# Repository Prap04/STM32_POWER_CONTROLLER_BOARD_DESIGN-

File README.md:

# STM32F103 Custom Control Board (PCB Project)

This project is a **custom-made PCB (Printed Circuit Board)** built around the **STM32F103C8T6 microcontroller**.  
The goal of this project was to learn how to design a **real hardware board** instead of only using ready-made development boards.

---

## Project Goal

To design a working STM32 board that includes:

- Stable power supply
- Communication ports (CAN, UART, I2C)
- Debugging support
- A PCB that is ready for manufacturing

---

## Main Components Used

| Part | What it Does |
|------|---------------|
| STM32F103C8T6 | Main microcontroller (the brain of the board) |
| CAN Transceiver | Allows CAN communication (used in robotics & industry) |
| UART Header | Used for serial communication and debugging |
| I2C Pins | Used to connect sensors |
| SWD Pins (SWIO, SWCLK) | Used to upload and debug firmware |
| Capacitors | Reduce noise and stabilize power |
| Voltage Regulation | Provides safe voltage to MCU |

---

## 🔧 What I Added Beyond the Tutorial

This board was inspired by Phil’s Lab STM32 tutorial, but I added extra features:

| Feature | Why I Added It |
|---------|----------------|
| CAN Communication | Used in industrial and robotic systems |
| Extra UART Access | Easy debugging and data output |
| I2C Support | To connect sensors |
| Better Debug Header | Easy firmware upload and testing |

---

## ⚡ Power Design (Simple Explanation)

- Small capacitors placed near MCU to reduce noise
- Bigger capacitors used to keep voltage stable
- Ground plane used to make signals cleaner

---

## 🧩 PCB Design Steps I Followed

1. Created the schematic (circuit diagram)
2. Chose the components
3. Placed components on PCB
4. Checked 3D view to see board shape
5. Routed connections
6. Ran DRC (error check)
7. Generated Gerber files
8. Prepared BOM list

---

## 🧪 How the Board Can Be Tested

If powering the board for the first time:

1. Check voltage using multimeter
2. Check clock signal
3. Upload firmware using ST-Link and SWD pins
4. Test UART communication on PC
5. Check I2C sensor connection
6. Test CAN communication

---

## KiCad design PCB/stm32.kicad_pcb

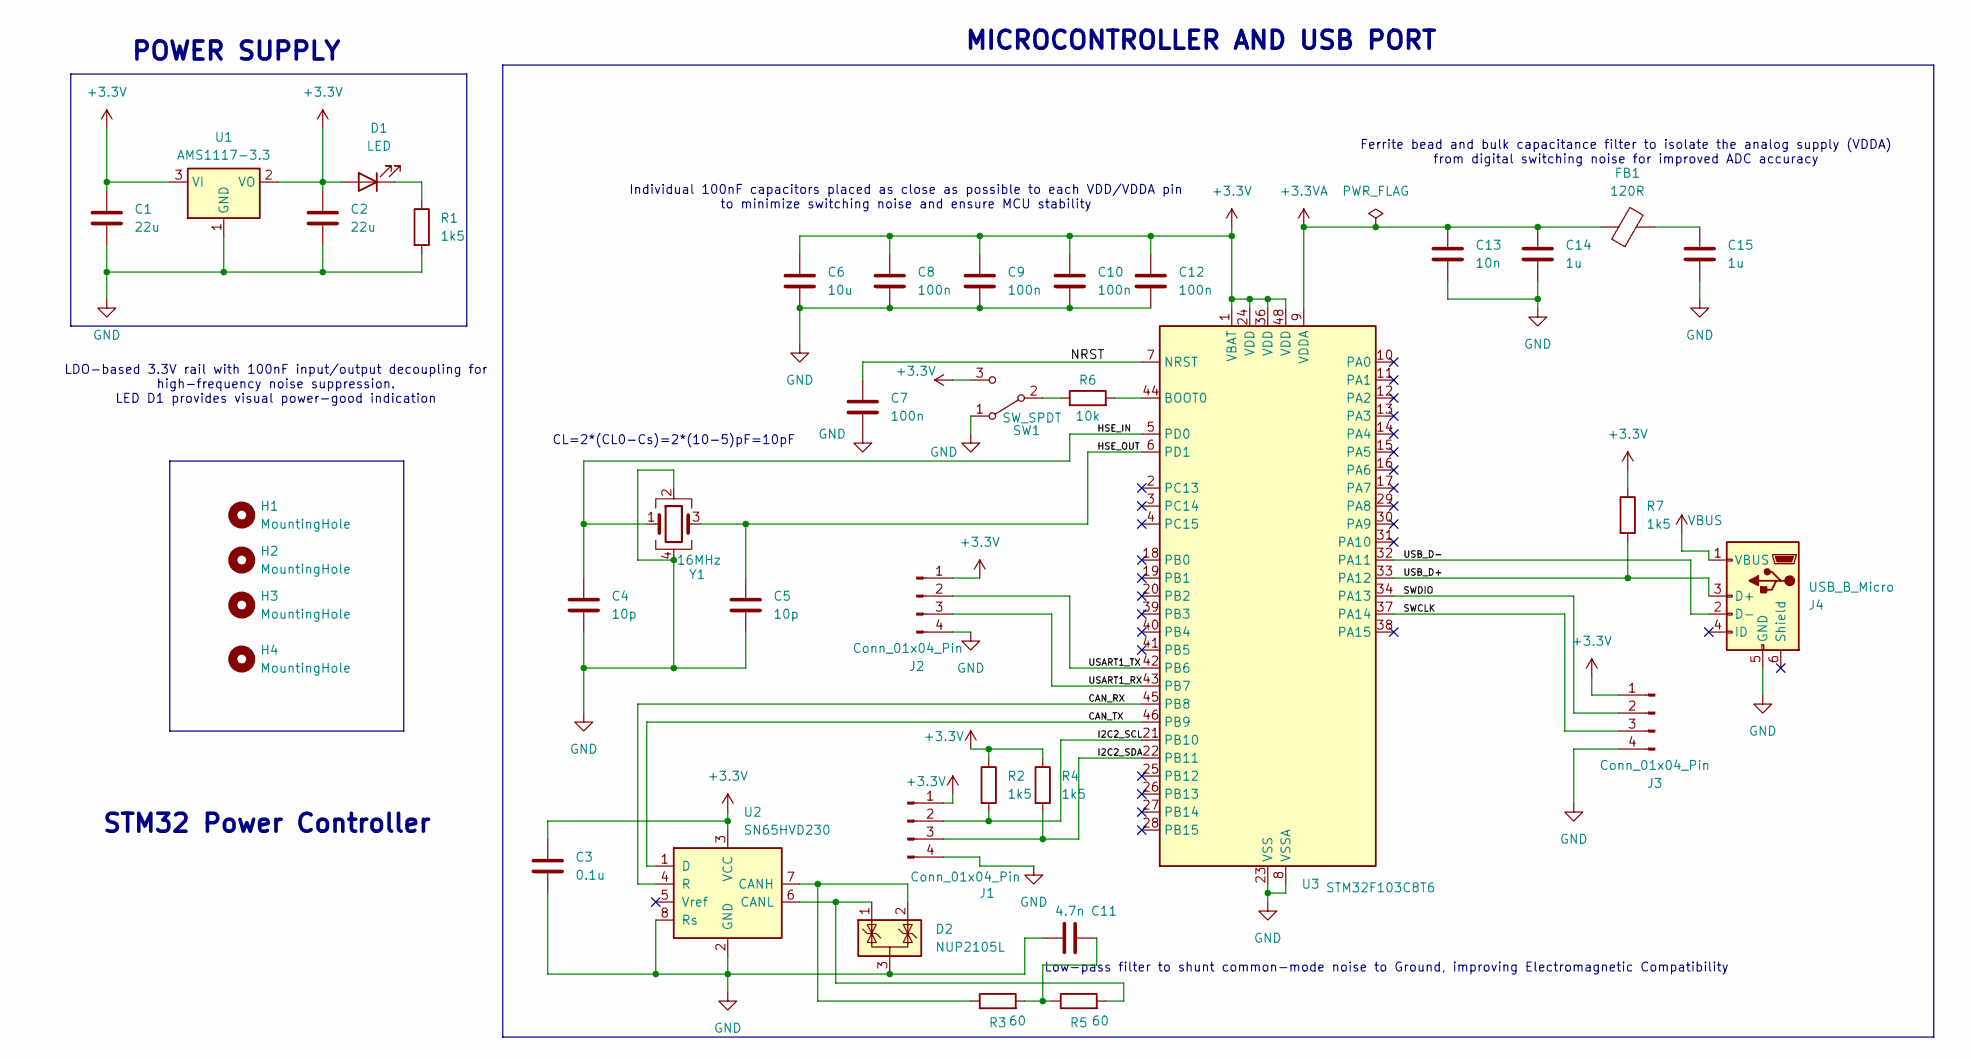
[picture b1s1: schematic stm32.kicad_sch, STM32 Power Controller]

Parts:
C1, C2: 22u; C_0805_2012Metric
C3: 0.1u; C_0402_1005Metric
C4, C5: 10p; C_0402_1005Metric
C6: 10u; C_0603_1608Metric
C7, C8, C9, C10, C12: 100n; C_0402_1005Metric
C11: 4.7n; C_0402_1005Metric
C13: 10n; C_0402_1005Metric
C14, C15: 1u; C_0402_1005Metric
D1: LED; LED_0603_1608Metric
D2: NUP2105L; SOT-23
FB1: 120R; L_0603_1608Metric
H1, H2, H3, H4: MountingHole; MountingHole_2.2mm_M2
J1, J2, J3: Conn_01x04_Pin; PinHeader_1x04_P2.54mm_Vertical
J4: USB_B_Micro; USB_Micro-B_Wuerth_629105150521
R1, R2, R4, R7: 1k5; R_0402_1005Metric
R3, R5: 60; R_0402_1005Metric
R6: 10k; R_0402_1005Metric
SW1: SW_SPDT; SW_SPDT_PCM12
U1: AMS1117-3.3; SOT-223-3_TabPin2
U2: SN65HVD230; SOIC-8_3.9x4.9mm_P1.27mm
U3: STM32F103C8T6; LQFP-48_7x7mm_P0.5mm
Y1: 16MHz; Crystal_SMD_3225-4Pin_3.2x2.5mm

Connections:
+3.3V: C1.1, C2.1, C3.1, C6.1, C8.1, C9.1, C10.1, C12.1, D1.2 (A), J1.1, J2.1, J3.1, R2.1, R4.1, R7.1, SW1.3 (C), U1.2 (VO), U1.3 (VI), U2.3 (VCC), U3.1 (VBAT), U3.24 (VDD), U3.36 (VDD), U3.48 (VDD)
+3.3VA: C13.1, C14.1, FB1.1, U3.9 (VDDA)
/CAN_RX: U2.4 (R), U3.45 (PB8)
/CAN_TX: U2.1 (D), U3.46 (PB9)
/HSE_IN: C4.1, U3.5 (PD0), Y1.1
/HSE_OUT: C5.1, U3.6 (PD1), Y1.3
/I2C2_SCL: J1.2, R2.2, U3.21 (PB10)
/I2C2_SDA: J1.3, R4.2, U3.22 (PB11)
/NRST: C7.1, U3.7 (NRST)
/SWCLK: J3.3, U3.37 (PA14)
/SWDIO: J3.2, U3.34 (PA13)
/USART1_RX: J2.3, U3.43 (PB7)
/USART1_TX: J2.2, U3.42 (PB6)
/USB_D+: J4.3 (D+), R7.2, U3.33 (PA12)
/USB_D-: J4.2 (D-), U3.32 (PA11)
GND: C1.2, C2.2, C3.2, C4.2, C5.2, C6.2, C7.2, C8.2, C9.2, C10.2, C11.1, C12.2, C13.2, C14.2, C15.2, D2.3 (A), J1.4, J2.4, J3.4, J4.5 (GND), R1.2, SW1.1 (A), U1.1 (GND), U2.2 (GND), U2.8 (Rs), U3.8 (VSSA), U3.23 (VSS), U3.35 (VSS), U3.47 (VSS), Y1.2, Y1.4
unnamed: C11.2, R3.2, R5.1
unnamed: C15.1, FB1.2
unnamed: D1.1 (K), R1.1
unnamed: R6.1, SW1.2 (B)
unnamed: D2.2 (K), R3.1, U2.7 (CANH)
unnamed: D2.1 (K), R5.2, U2.6 (CANL)
unnamed: R6.2, U3.44 (BOOT0)
VBUS: J4.1 (VBUS)

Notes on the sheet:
CL=2*(CL0-Cs)=2*(10-5)pF=10pF
MICROCONTROLLER AND USB PORT
Low-pass filter to shunt common-mode noise to Ground, improving Electromagnetic Compatibility
Ferrite bead and bulk capacitance filter to isolate the analog supply (VDDA) from digital switching noise for improved ADC accuracy
Individual 100nF capacitors placed as close as possible to each VDD/VDDA pin to minimize switching noise and ensure MCU stability
STM32 Power Controller
LDO-based 3.3V rail with 100nF input/output decoupling for high-frequency noise suppression. LED D1 provides visual power-good indication
POWER SUPPLY

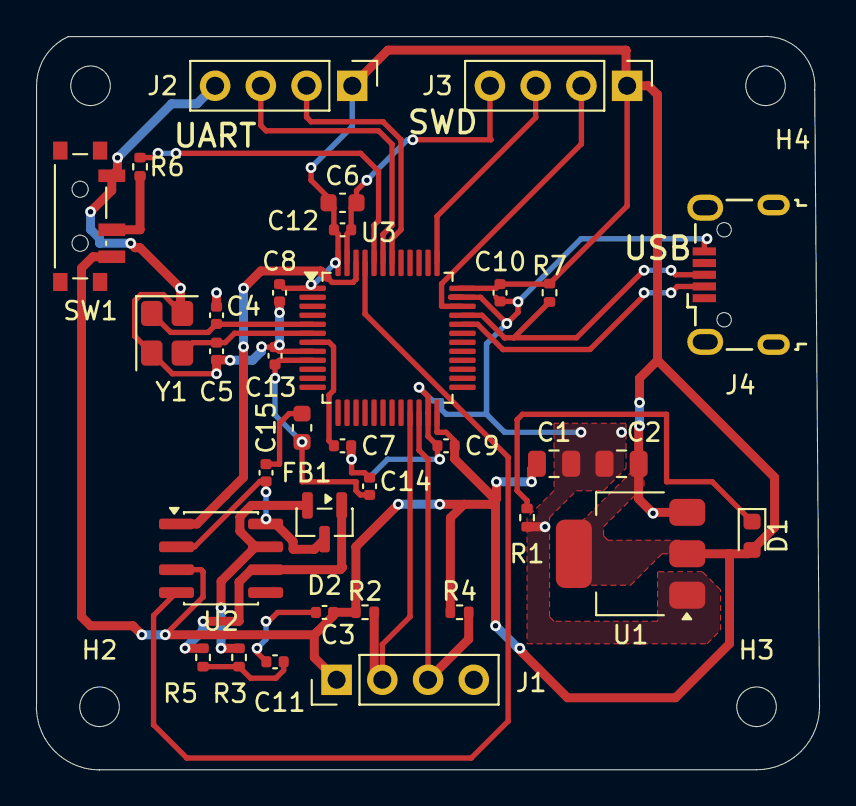
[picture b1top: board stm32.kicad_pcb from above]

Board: 2 copper layers, 43.5 x 40.7 mm, 38 parts (0 on the bottom side), 23 nets.

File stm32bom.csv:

"Reference","Qty","Value","DNP","Exclude from BOM","Exclude from Board","Footprint","Datasheet"
"C1,C2","2","22u","","","","Capacitor_SMD:C_0805_2012Metric","~"
"C3","1","0.1u","","","","Capacitor_SMD:C_0402_1005Metric","~"
"C4,C5","2","10p","","","","Capacitor_SMD:C_0402_1005Metric","~"
"C6","1","10u","","","","Capacitor_SMD:C_0603_1608Metric","~"
"C7,C8,C9,C10,C12","5","100n","","","","Capacitor_SMD:C_0402_1005Metric","~"
"C11","1","4.7n","","","","Capacitor_SMD:C_0402_1005Metric","~"
"C13","1","10n","","","","Capacitor_SMD:C_0402_1005Metric","~"
"C14,C15","2","1u","","","","Capacitor_SMD:C_0402_1005Metric","~"
"D1","1","LED","","","","LED_SMD:LED_0603_1608Metric","~"
"D2","1","NUP2105L","","","","Package_TO_SOT_SMD:SOT-23","https://www.onsemi.com/pub_link/Collateral/NUP2105L-D.PDF"
"FB1","1","120R","","","","Inductor_SMD:L_0603_1608Metric","~"
"H1,H2,H3,H4","4","MountingHole","","Excluded from BOM","","MountingHole:MountingHole_2.2mm_M2","~"
"J1,J2,J3","3","Conn_01x04_Pin","","","","Connector_PinHeader_2.54mm:PinHeader_1x04_P2.54mm_Vertical","~"
"J4","1","USB_B_Micro","","","","Connector_USB:USB_Micro-B_Wuerth_629105150521","~"
"R1,R2,R4,R7","4","1k5","","","","Resistor_SMD:R_0402_1005Metric","~"
"R3,R5","2","60","","","","Resistor_SMD:R_0402_1005Metric","~"
"R6","1","10k","","","","Resistor_SMD:R_0402_1005Metric","~"
"SW1","1","SW_SPDT","","","","Button_Switch_SMD:SW_SPDT_PCM12","~"
"U1","1","AMS1117-3.3","","","","Package_TO_SOT_SMD:SOT-223-3_TabPin2","http://www.advanced-monolithic.com/pdf/ds1117.pdf"
"U2","1","SN65HVD230","","","","Package_SO:SOIC-8_3.9x4.9mm_P1.27mm","http://www.ti.com/lit/ds/symlink/sn65hvd230.pdf"
"U3","1","STM32F103C8T6","","","","Package_QFP:LQFP-48_7x7mm_P0.5mm","https://www.st.com/resource/en/datasheet/stm32f103c8.pdf"
"Y1","1","16MHz","","","","Crystal:Crystal_SMD_3225-4Pin_3.2x2.5mm","~"

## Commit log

2026-02-08 Update README to simplify project title
    Removed unnecessary project title from README.
2026-02-08 Initial commit
    Initial upload: PCB project files, Gerbers, BOM, README
